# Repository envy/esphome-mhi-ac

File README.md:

# esphome-mhi-ac
Component for esphome to use SPI to connect to a Mitsubishi Heavy Industries AC

# Authors
This code is based on https://github.com/tfyoung/esphome-MHIHeatPump

## ESPHome Config
Example config:

```yaml
external_components:
  - source: github://envy/esphome-mhi-ac

# Exactly one mhi_ac must exist in the configuration
mhi_ac:
  # Optional configuration with default values below
  processing_time: 100  # Time in ms that the component should communicate with the AC during each loop cycle.
  use_extended_frame_format: False  # Enable features such as horizontal vanes and 3D Auto.

climate:
  - platform: mhi_ac
    name: AC
    # Optional configuration with default values below
    vertical_swing_off_position: 2  # When swing is turned off, this is the position the vertical vanes will go to. Valid values: 1, 2, 3, 4
    horizontal_swing_off_position: 2  # When swing is turned off, this is the position the horizontal vanes will go to. Valid values: 1, 2, 3, 4, 5, 6, 7

sensor:
  - platform: mhi_ac
    # All sensors below are optional.
    outdoor_temperature:
      name: Outdoor Temperature
    current:
      name: Current
    energy:
      name: Energy

select:
  - platform: mhi_ac
    # All selects below are optional
    vertical_vanes:
      name: Vertical Vanes
      # It is possible to configure the names in the select, e.g., to translate them like so:
      up: Up
      mid_up: Mid Up
      mid_down: Mid Down
      down: Down
      swing: Swing
    horizontal_vanes:
      name: Horizontal Vanes
      # It is possible to configure the names in the select, e.g., to translate them like so:
      left: Left
      mid_left: Mid Left
      middle: Middle
      mid_right: Mid Right
      right: Right
      inner: Inner
      outer: Outer
      swing: Swing

```

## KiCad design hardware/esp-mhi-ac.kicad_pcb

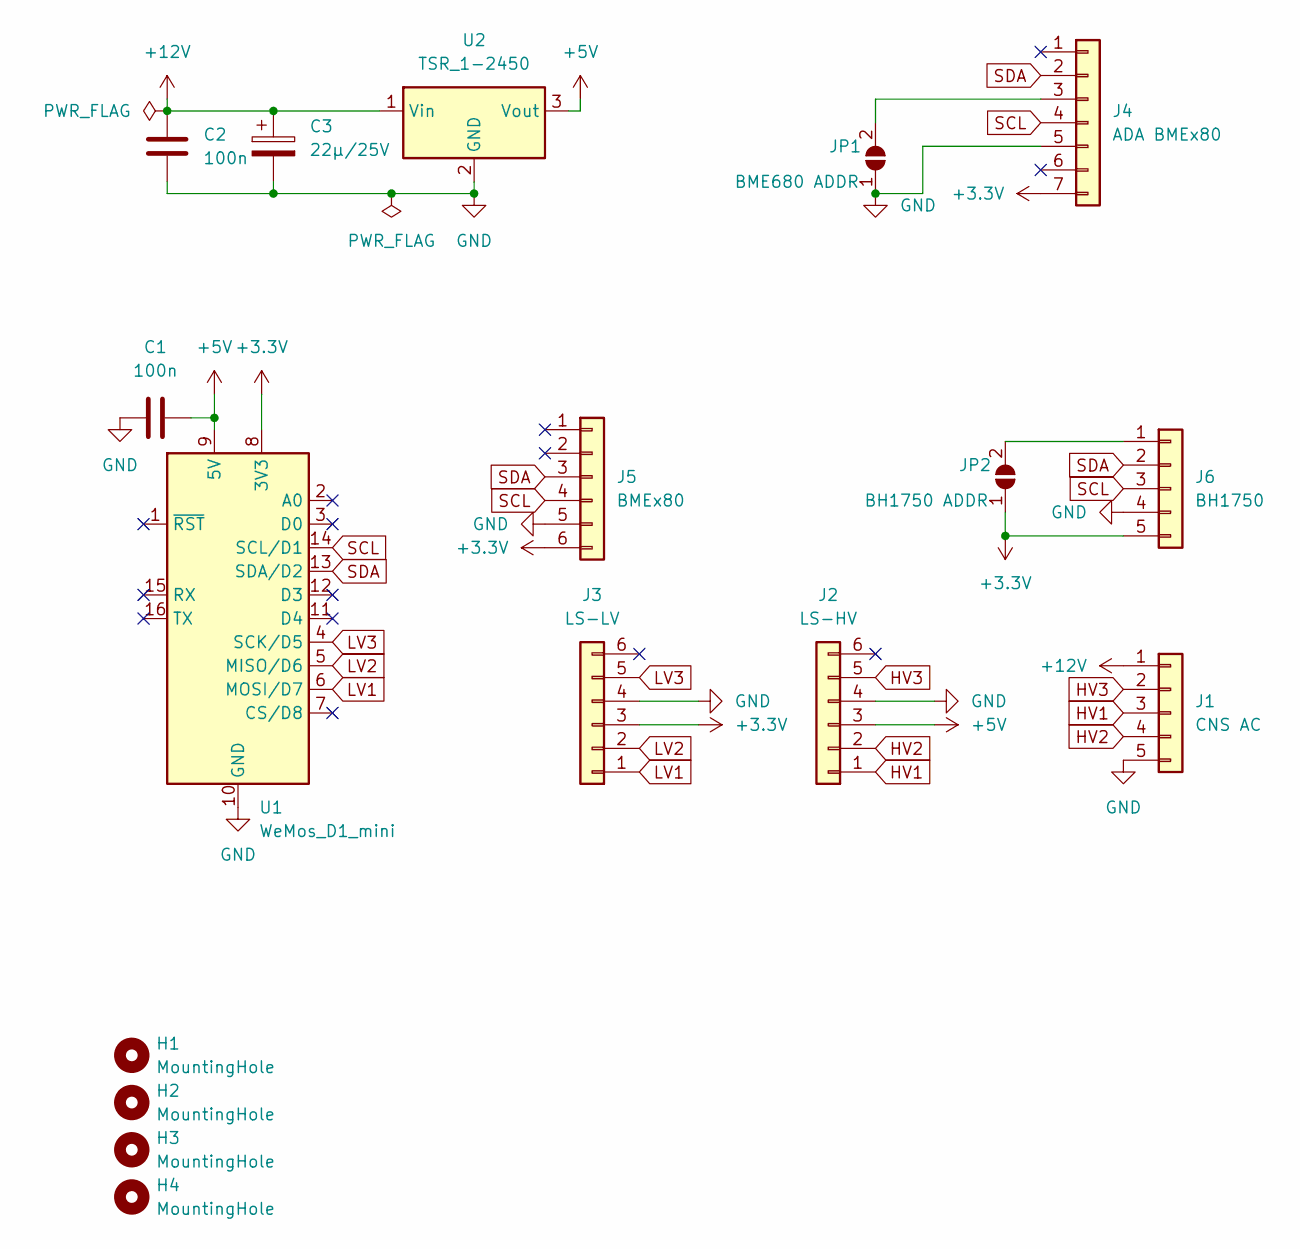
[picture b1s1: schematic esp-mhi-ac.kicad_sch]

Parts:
C1, C2: 100n; C_Disc_D4.7mm_W2.5mm_P5.00mm
C3: 22µ/25V; CP_Radial_D6.3mm_P2.50mm
H1, H2, H3, H4: MountingHole; MountingHole_3.2mm_M3
J1: CNS AC; JST_XH_S5B-XH-A_1x05_P2.50mm_Horizontal
J2: LS-HV; PinSocket_1x06_P2.54mm_Vertical
J3: LS-LV; PinSocket_1x06_P2.54mm_Vertical
J4: ADA BMEx80; PinSocket_1x07_P2.54mm_Vertical
J5: BMEx80; PinSocket_1x06_P2.54mm_Vertical
J6: BH1750; PinSocket_1x05_P2.54mm_Vertical
JP1: BME680 ADDR; SolderJumper-2_P1.3mm_Open_TrianglePad1.0x1.5mm
JP2: BH1750 ADDR; SolderJumper-2_P1.3mm_Open_TrianglePad1.0x1.5mm
U1: WeMos_D1_mini; WEMOS_D1_mini_light
U2: TSR_1-2450; Converter_DCDC_TRACO_TSR-1_THT

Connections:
+3.3V: J3.3, J4.7, J5.6, J6.5, JP2.1 (A), U1.8 (3V3)
+5V: C1.2, J2.3, U1.9 (5V), U2.3 (Vout)
+12V: C2.1, C3.1, J1.1, U2.1 (Vin)
GND: C1.1, C2.2, C3.2, J1.5, J2.4, J3.4, J4.5, J5.5, J6.4, JP1.1 (A), U1.10 (GND), U2.2 (GND)
HV1: J1.3, J2.1
HV2: J1.4, J2.2
HV3: J1.2, J2.5
LV1: J3.1, U1.6 (MOSI/D7)
LV2: J3.2, U1.5 (MISO/D6)
LV3: J3.5, U1.4 (SCK/D5)
unnamed: J4.3, JP1.2 (B)
unnamed: J6.1, JP2.2 (B)
SCL: J4.4, J5.4, J6.3, U1.14 (SCL/D1)
SDA: J4.2, J5.3, J6.2, U1.13 (SDA/D2)

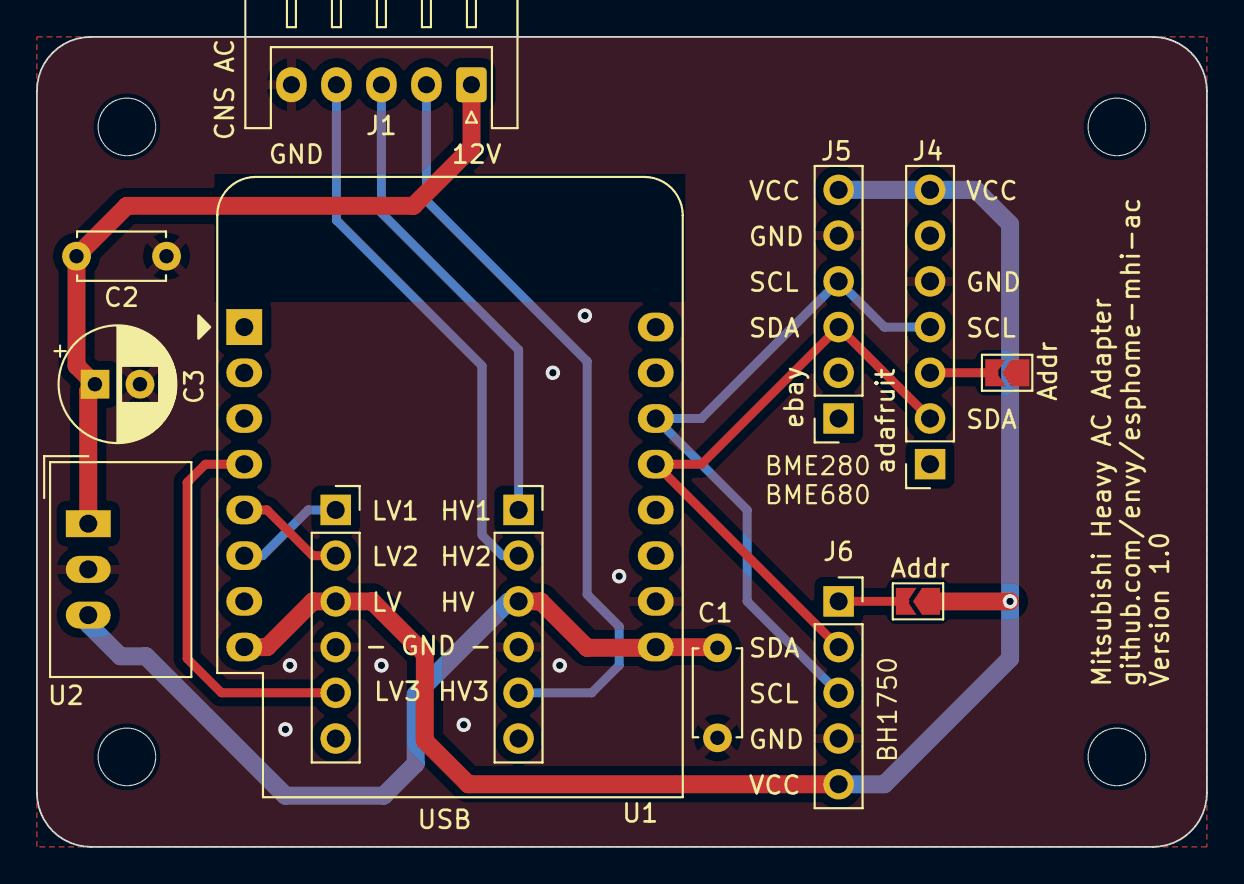
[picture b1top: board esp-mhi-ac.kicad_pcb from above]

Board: 2 copper layers, 65.0 x 45.0 mm, 17 parts (0 on the bottom side), 14 nets.

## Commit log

2023-07-24 refactorings
2023-07-24 update ctrl lib
2023-07-24 more sensors
2023-07-24 ignore some irrelevant statuses
2023-07-28 vertical vanes select
2023-07-28 climate to async codegen
2023-07-28 component to async
2023-07-28 fix temp, add check if comm is working
2023-07-28 add default off position for vanes
2023-08-05 add hardware
2023-08-16 update hardware
2024-02-18 add case
2024-03-03 update case
2024-03-03 update core lib
2024-03-03 update pin definitions for esp8366 and esp32
2024-03-03 support for horizontal vanes
2025-06-20 update to new esphome requirements
2025-06-20 add protection state sensor
2025-12-02 esphome 2025.11 compat
